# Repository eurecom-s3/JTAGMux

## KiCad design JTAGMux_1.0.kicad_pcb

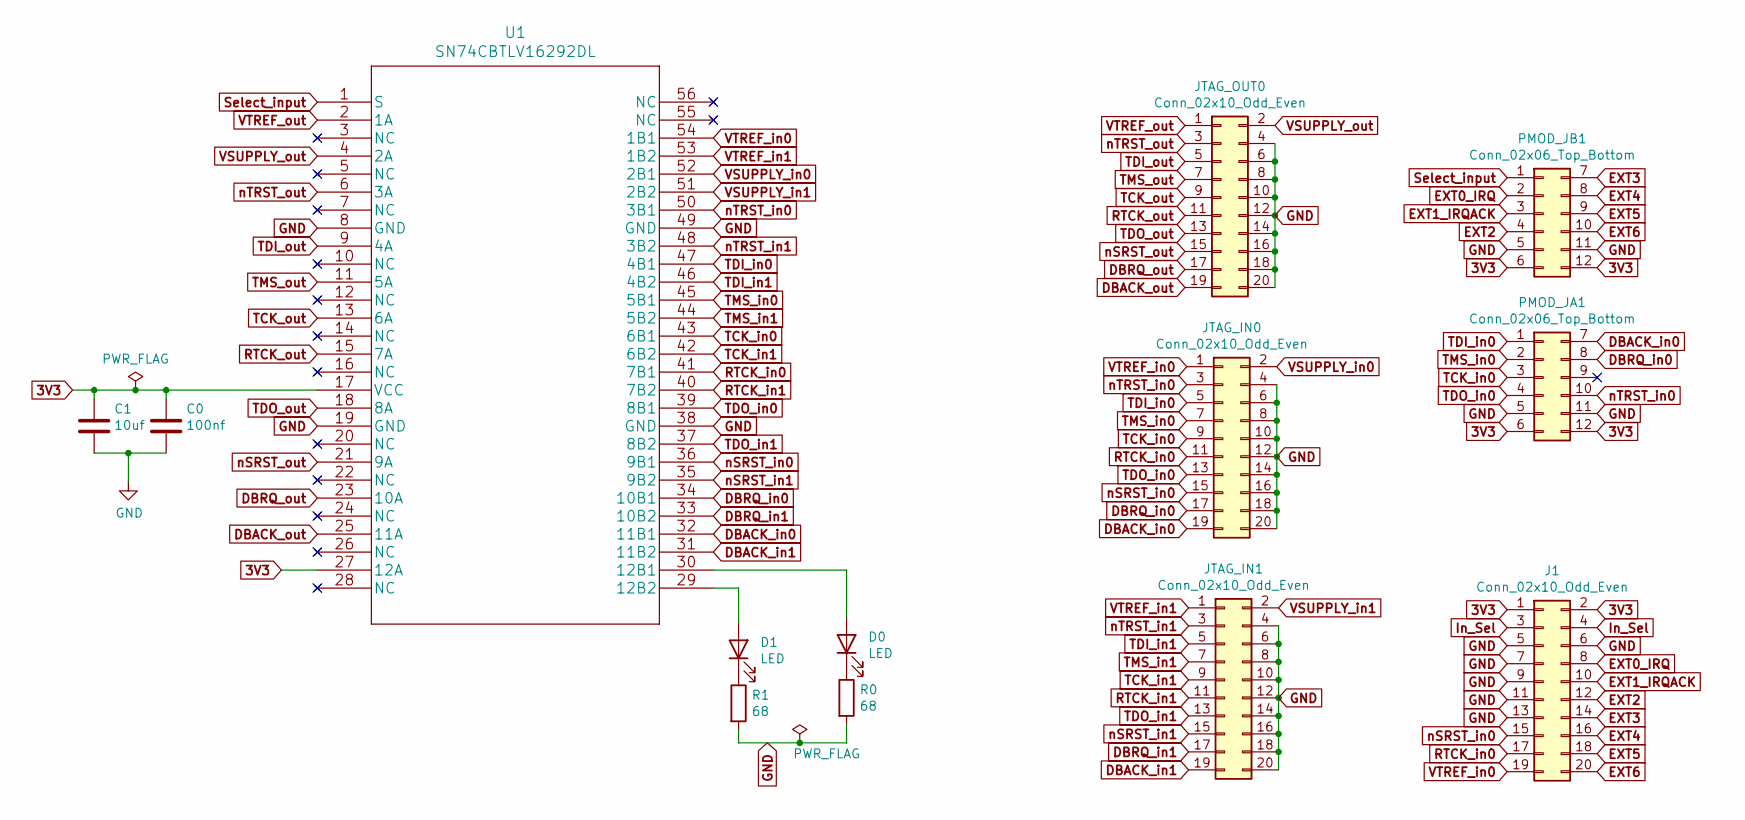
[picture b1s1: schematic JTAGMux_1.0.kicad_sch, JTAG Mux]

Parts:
C0: 100nf; C_0603_1608Metric
C1: 10uf; C_0603_1608Metric
D0, D1: LED; LED_0603_1608Metric
J1: Conn_02x10_Odd_Even; PinHeader_2x10_P2.54mm_Vertical
JTAG_IN0, JTAG_IN1: Conn_02x10_Odd_Even; PinHeader_2x10_P2.54mm_Vertical
JTAG_OUT0: Conn_02x10_Odd_Even; PinHeader_2x10_P2.54mm_Vertical
PMOD_JA1: Conn_02x06_Top_Bottom; PinHeader_2x06_P2.54mm_Horizontal_pmod
PMOD_JB1: Conn_02x06_Top_Bottom; PinHeader_2x06_P2.54mm_Horizontal_pmod
R0, R1: 68; R_0603_1608Metric
U1: SN74CBTLV16292DL; SSOP-56_7.5x18.5mm_Pitch0.635mm

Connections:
3V3: C0.1, C1.1, J1.1, J1.2, PMOD_JA1.6, PMOD_JA1.12, PMOD_JB1.6, PMOD_JB1.12, U1.17 (VCC), U1.27 (12A)
DBACK_in0: JTAG_IN0.19, PMOD_JA1.7, U1.32 (11B1)
DBACK_in1: JTAG_IN1.19, U1.31 (11B2)
DBACK_out: JTAG_OUT0.19, U1.25 (11A)
DBRQ_in0: JTAG_IN0.17, PMOD_JA1.8, U1.34 (10B1)
DBRQ_in1: JTAG_IN1.17, U1.33 (10B2)
DBRQ_out: JTAG_OUT0.17, U1.23 (10A)
EXT0_IRQ: J1.8, PMOD_JB1.2
EXT1_IRQACK: J1.10, PMOD_JB1.3
EXT2: J1.12, PMOD_JB1.4
EXT3: J1.14, PMOD_JB1.7
EXT4: J1.16, PMOD_JB1.8
EXT5: J1.18, PMOD_JB1.9
EXT6: J1.20, PMOD_JB1.10
GND: C0.2, C1.2, J1.5, J1.6, J1.7, J1.9, J1.11, J1.13, JTAG_IN0.4, JTAG_IN0.6, JTAG_IN0.8, JTAG_IN0.10, JTAG_IN0.12, JTAG_IN0.14, JTAG_IN0.16, JTAG_IN0.18, JTAG_IN0.20, JTAG_IN1.4, JTAG_IN1.6, JTAG_IN1.8, JTAG_IN1.10, JTAG_IN1.12, JTAG_IN1.14, JTAG_IN1.16, JTAG_IN1.18, JTAG_IN1.20, JTAG_OUT0.4, JTAG_OUT0.6, JTAG_OUT0.8, JTAG_OUT0.10, JTAG_OUT0.12, JTAG_OUT0.14, JTAG_OUT0.16, JTAG_OUT0.18, JTAG_OUT0.20, PMOD_JA1.5, PMOD_JA1.11, PMOD_JB1.5, PMOD_JB1.11, R0.2, R1.2, U1.8 (GND), U1.19 (GND), U1.38 (GND), U1.49 (GND)
In_Sel: J1.3, J1.4
unnamed: D0.1 (K), R0.1
unnamed: D0.2 (A), U1.30 (12B1)
unnamed: D1.1 (K), R1.1
unnamed: D1.2 (A), U1.29 (12B2)
RTCK_in0: J1.17, JTAG_IN0.11, U1.41 (7B1)
RTCK_in1: JTAG_IN1.11, U1.40 (7B2)
RTCK_out: JTAG_OUT0.11, U1.15 (7A)
Select_input: PMOD_JB1.1, U1.1 (S)
TCK_in0: JTAG_IN0.9, PMOD_JA1.3, U1.43 (6B1)
TCK_in1: JTAG_IN1.9, U1.42 (6B2)
TCK_out: JTAG_OUT0.9, U1.13 (6A)
TDI_in0: JTAG_IN0.5, PMOD_JA1.1, U1.47 (4B1)
TDI_in1: JTAG_IN1.5, U1.46 (4B2)
TDI_out: JTAG_OUT0.5, U1.9 (4A)
TDO_in0: JTAG_IN0.13, PMOD_JA1.4, U1.39 (8B1)
TDO_in1: JTAG_IN1.13, U1.37 (8B2)
TDO_out: JTAG_OUT0.13, U1.18 (8A)
TMS_in0: JTAG_IN0.7, PMOD_JA1.2, U1.45 (5B1)
TMS_in1: JTAG_IN1.7, U1.44 (5B2)
TMS_out: JTAG_OUT0.7, U1.11 (5A)
VSUPPLY_in0: JTAG_IN0.2, U1.52 (2B1)
VSUPPLY_in1: JTAG_IN1.2, U1.51 (2B2)
VSUPPLY_out: JTAG_OUT0.2, U1.4 (2A)
VTREF_in0: J1.19, JTAG_IN0.1, U1.54 (1B1)
VTREF_in1: JTAG_IN1.1, U1.53 (1B2)
VTREF_out: JTAG_OUT0.1, U1.2 (1A)
nSRST_in0: J1.15, JTAG_IN0.15, U1.36 (9B1)
nSRST_in1: JTAG_IN1.15, U1.35 (9B2)
nSRST_out: JTAG_OUT0.15, U1.21 (9A)
nTRST_in0: JTAG_IN0.3, PMOD_JA1.10, U1.50 (3B1)
nTRST_in1: JTAG_IN1.3, U1.48 (3B2)
nTRST_out: JTAG_OUT0.3, U1.6 (3A)

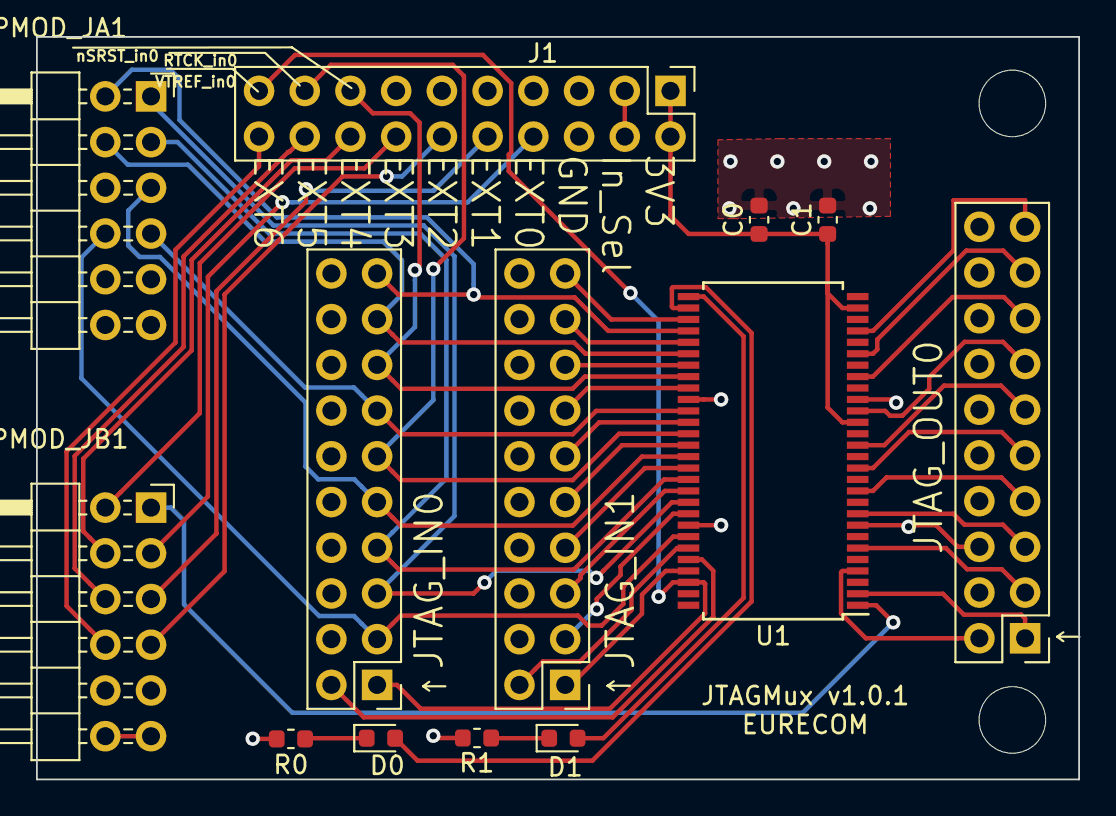
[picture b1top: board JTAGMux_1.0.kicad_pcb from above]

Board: 4 copper layers, 57.9 x 41.2 mm, 15 parts (0 on the bottom side), 48 nets.

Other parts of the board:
M1, M2: MountingHole_3.7mm

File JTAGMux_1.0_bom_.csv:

"Id";"Référence";"Boîtier";"Quantité";"Désignation";"Fournisseur et réf";
1;"PMOD_JB1,PMOD_JA1";"PinHeader_2x06_P2.54mm_Horizontal_pmod";2;"Conn_02x06_Top_Bottom";;;
2;"JTAG_IN0,JTAG_OUT0,JTAG_IN1,J1";"PinHeader_2x10_P2.54mm_Vertical";4;"Conn_02x10_Odd_Even";;;
3;"M2,M1";"MountingHole_3.7mm";2;"MountingHole_3.7mm";;;
4;"D1,D0";"LED_0603_1608Metric";2;"LED";;;
5;"U1";"SSOP-56_7.5x18.5mm_P0.635mm";1;"SN74CBTLV16292DL";;;
6;"R1,R0";"R_0603_1608Metric";2;"68";;;
7;"C1";"C_0603_1608Metric";1;"10uf";;;
8;"C0";"C_0603_1608Metric";1;"100nf";;;

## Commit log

2019-04-06 schematic
2019-04-12 complete version 1.0.0
2019-04-12 minor routing improvement + adding pdf and gerber files
2021-11-30 version 1.0.1
2024-12-11 Update to KiCad 8.0 with removal of rescue lefovers
2025-01-09 Moved SN74CBTLV16292 in local lib with proper naming
